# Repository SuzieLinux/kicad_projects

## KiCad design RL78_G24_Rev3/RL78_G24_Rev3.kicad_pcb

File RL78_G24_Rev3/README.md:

This board can use a RL78 G14 or G24, G24 is a newer device which is pin
compatible but uses a different program for configuration

The G14 uses applilet3 and the G24 uses the smart configurator.

I have not tested this board yet but it should work as it is based on other
working boards. If I find issues when I receive the boards I will make an
update to the design

The board runs at 3.3V.
The LCD is Chanruida 1.8 inch TFT LCD 128 × 160 color screen 
ST7735 SPI display LCD module with SD card slot arduino display display lcd

The ethernet adapter is a small board called W5500 SPI to LAN ethernet
network module

The keypad is a 4x5 keypad

The debugger used is E2 Lite. I have an adapter so you can connect the
debugger to it.

Feel free to use this board but if you are going to make money with it be
nice enough to make a donation on my website.

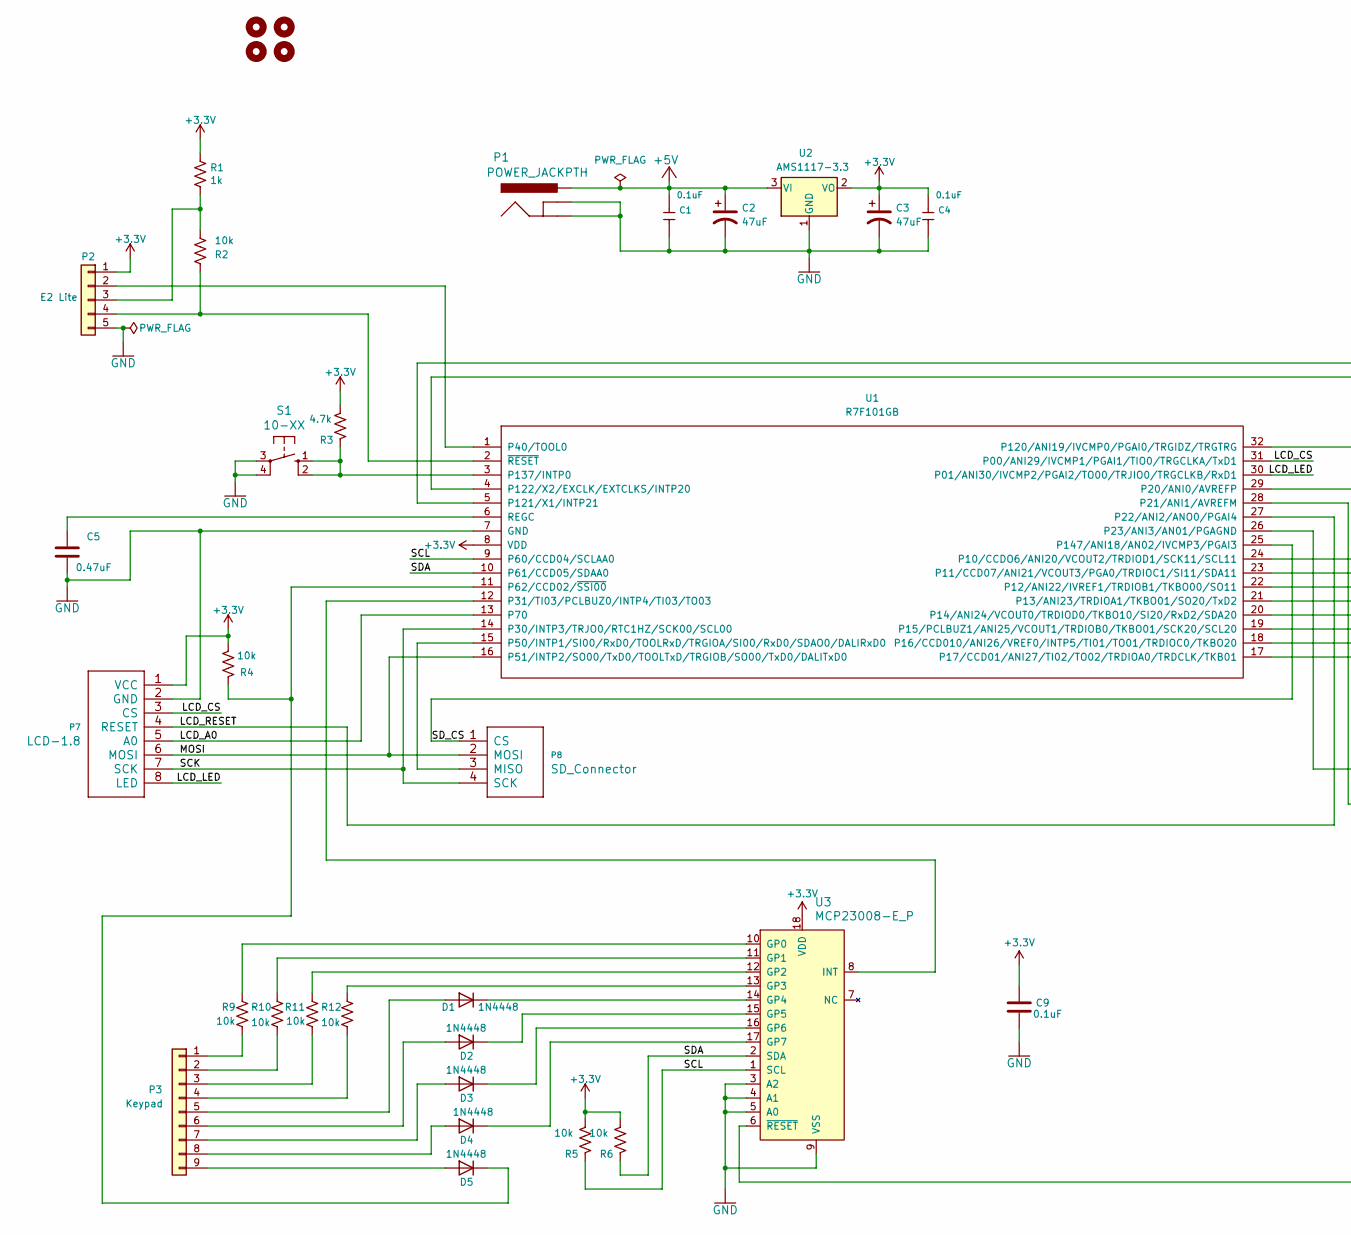
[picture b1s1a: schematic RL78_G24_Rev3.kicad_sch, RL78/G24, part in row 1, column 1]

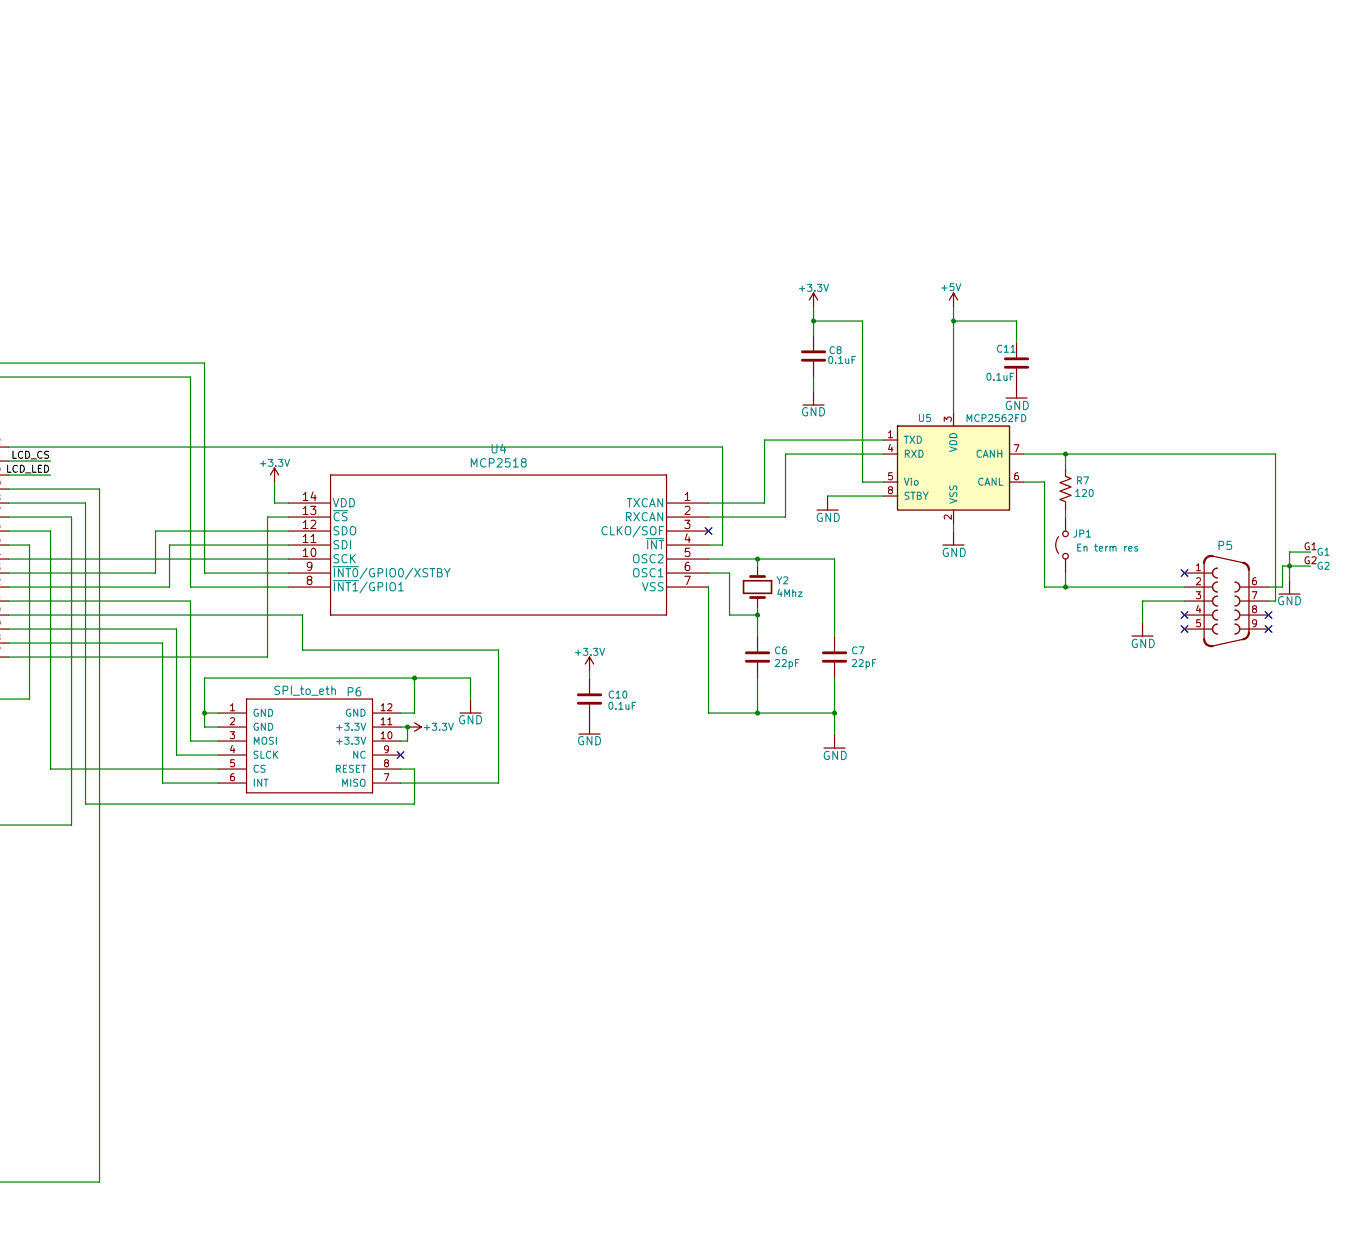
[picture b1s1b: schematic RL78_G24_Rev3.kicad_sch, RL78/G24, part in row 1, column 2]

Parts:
C1, C4: 0.1uF; C_0805_2012Metric_Pad1.18x1.45mm_HandSolder; MPN CC0603KRX7R9BB104; LCSC C14663
C2, C3: 47uF; CP_Radial_D6.3mm_P2.50mm
C5: 0.47uF; C_0805_2012Metric_Pad1.18x1.45mm_HandSolder
C6, C7: 22pF; C_0805_2012Metric_Pad1.18x1.45mm_HandSolder
C8, C9, C10, C11: 0.1uF; C_0805_2012Metric_Pad1.18x1.45mm_HandSolder
D1, D2, D3, D4, D5: 1N4448; D_DO-35_SOD27_P7.62mm_Horizontal
H1, H2, H3, H4: MountingHole; MountingHole_2.7mm_M2.5_DIN965_Pad
JP1: En term res; PinHeader_1x02_P2.54mm_Vertical
P1: POWER_JACKPTH; POWER_JACK_PTH
P2: E2 Lite; PinHeader_1x05_P2.54mm_Vertical
P3: Keypad; PinHeader_1x09_P2.54mm_Vertical
P5: F09HP
P6: SPI_to_eth
P7: LCD-1.8; PinHeader_1x08_P2.54mm_Vertical
P8: SD_Connector; PinHeader_1x04_P2.54mm_Vertical
R1: 1k; R_0805_2012Metric
R2, R9, R10, R11, R12: 10k; R_0805_2012Metric
R3: 4.7k; R_0805_2012Metric_Pad1.20x1.40mm_HandSolder
R4, R5, R6: 10k; R_0805_2012Metric_Pad1.20x1.40mm_HandSolder
R7: 120; R_2512_6332Metric_Pad1.40x3.35mm_HandSolder
S1: 10-XX; B3F-10XX
U1: R7F101GB; LQFP-32_7x7mm
U2: AMS1117-3.3; SOT-223-3_TabPin2; LCSC C6186
U3: MCP23008-E_P; DIP-18_W7.62mm; MPN MCP23008-E/P; Digi-Key_PN MCP23008-E/P-ND
U4: MCP2518; MCP2518FD
U5: MCP2562FD; DIP-8_W7.62mm
Y2: 4Mhz; Crystal_HC49-4H_Vertical

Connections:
+3.3V: C3.1, C4.1, C8.1, C9.1, C10.1, P2.1, P6.10 (+3.3V), P6.11 (+3.3V), P7.1 (VCC), R1.1, R3.2, R4.2, R5.2, R6.2, U1.8 (VDD), U2.2 (VO), U3.18 (VDD), U4.14 (VDD), U5.5 (Vio)
+5V: C1.1, C2.1, C11.1, P1.PWR, U2.3 (VI), U5.3 (VDD)
/LCD_A0: P7.5 (A0), U1.13 (P70)
/LCD_CS: P7.3 (CS), U1.31 (P00/ANI29/IVCMP1/PGAI1/TIO0/TRGCLKA/TxD1)
/LCD_LED: P7.8 (LED), U1.30 (P01/ANI30/IVCMP2/PGAI2/TO00/TRJIO0/TRGC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)
/LCD_RESET: P7.4 (RESET), U1.27 (P22/ANI2/ANO0/PGAI4)
/MOSI: P7.6 (MOSI), P8.2 (MOSI), U1.16 (P51/INTP2/SO00/TxD0/TOOLTxD/TRGIOB/SO00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)
/SCK: P7.7 (SCK), P8.4 (SCK), U1.14 (P30/INTP3/TRJO0/RTC1HZ/SCK00/SCL00)
/SCL: R5.1, U1.9 (P60/CCD04/SCLAA0), U3.1 (SCL)
/SDA: R6.1, U1.10 (P61/CCD05/SDAA0), U3.2 (SDA)
/SD_CS: P8.1 (CS), U1.25 (P147/ANI18/AN02/IVCMP3/PGAI3)
GND: C1.2, C2.2, C3.2, C4.2, C5.2, C6.2, C7.2, C8.2, C9.2, C10.2, C11.2, P1.GND, P1.GNDBREAK, P2.5, P5.3, P5.6, P5.G1, P5.G2, P6.1 (GND), P6.2 (GND), P6.12 (GND), P7.2 (GND), S1.3, S1.4 (P1), U1.7 (GND), U2.1 (GND), U3.3 (A2), U3.4 (A1), U3.5 (A0), U3.9 (VSS), U4.7 (VSS), U5.2 (VSS), U5.8 (STBY)
unnamed: D1.2 (A), P3.5
unnamed: D1.1 (K), U3.14 (GP4)
unnamed: D2.2 (A), P3.6
unnamed: D2.1 (K), U3.15 (GP5)
unnamed: D3.2 (A), P3.7
unnamed: D3.1 (K), U3.16 (GP6)
unnamed: D4.2 (A), P3.8
unnamed: D4.1 (K), U3.17 (GP7)
unnamed: D5.2 (A), P3.9
unnamed: D5.1 (K), R4.1, U1.11 (P62/CCD02/~SSI00)
unnamed: JP1.1 (A), P5.2, U5.6 (CANL)
unnamed: JP1.2 (B), R7.2
unnamed: P2.2, U1.1 (P40/TOOL0)
unnamed: P2.3, R1.2, R2.1
unnamed: P2.4, R2.2, U1.2 (~RESET)
unnamed: P3.1, R9.2
unnamed: P3.2, R10.2
unnamed: P3.3, R11.2
unnamed: P3.4, R12.2
unnamed: P6.5 (CS), U1.26 (P23/ANI3/AN01/PGAGND)
unnamed: P6.6 (INT), U1.18 (P16/CCD010/ANI26/VREF0/INTP5/TI01/TO01/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)
unnamed: P6.7 (MISO), U1.20 (P14/ANI24/VCOUT0/TRDIOD0/TKBO10/SI20/Rx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)
unnamed: P6.3 (MOSI), U1.21 (P13/ANI23/TRDIOA1/TKBO01/SO20/TxD2)
unnamed: P6.8 (RESET), U1.28 (P21/ANI1/AVREFM)
unnamed: P6.4 (SLCK), U1.19 (P15/PCLBUZ1/ANI25/VCOUT1/TRDIOB0/TKBO01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)
unnamed: P8.3 (MISO), U1.15 (P50/INTP1/SI00/RxD0/TOOLRxD/TRGIOA/SI00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)
unnamed: R3.1, S1.1 (S), S1.2 (S1), U1.3 (P137/INTP0)
unnamed: U1.24 (P10/CCDO6/ANI20/VCOUT2/TRDIOD1/SCK11/SC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), U4.10 (SCK)
unnamed: U1.23 (P11/CCD07/ANI21/VCOUT3/PGA0/TRDIOC1/SI1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), U4.12 (SDO)
unnamed: U1.22 (P12/ANI22/IVREF1/TRDIOB1/TKBO00/SO11), U4.11 (SDI)
unnamed: U1.17 (P17/CCD01/ANI27/TI02/TO02/TRDIOA0/TRDCL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), U4.13 (~CS)
unnamed: U1.29 (P20/ANI0/AVREFP), U3.6 (~RESET)
unnamed: U1.12 (P31/TI03/PCLBUZ0/INTP4/TI03/TO03), U3.8 (INT)
unnamed: U1.32 (P120/ANI19/IVCMP0/PGAI0/TRGIDZ/TRGTRG), U4.4 (~INT)
unnamed: U1.5 (P121/X1/INTP21), U4.9 (~INT0/GPIO0/XSTBY)
unnamed: U1.4 (P122/X2/EXCLK/EXTCLKS/INTP20), U4.8 (~INT1/GPIO1)
unnamed: C5.1, U1.6 (REGC)
unnamed: R9.1, U3.10 (GP0)
unnamed: R10.1, U3.11 (GP1)
unnamed: R11.1, U3.12 (GP2)
unnamed: R12.1, U3.13 (GP3)
unnamed: C6.1, U4.6 (OSC1), Y2.2
unnamed: C7.1, U4.5 (OSC2), Y2.1
unnamed: U4.2 (RXCAN), U5.4 (RXD)
unnamed: U4.1 (TXCAN), U5.1 (TXD)
unnamed: P5.7, R7.1, U5.7 (CANH)

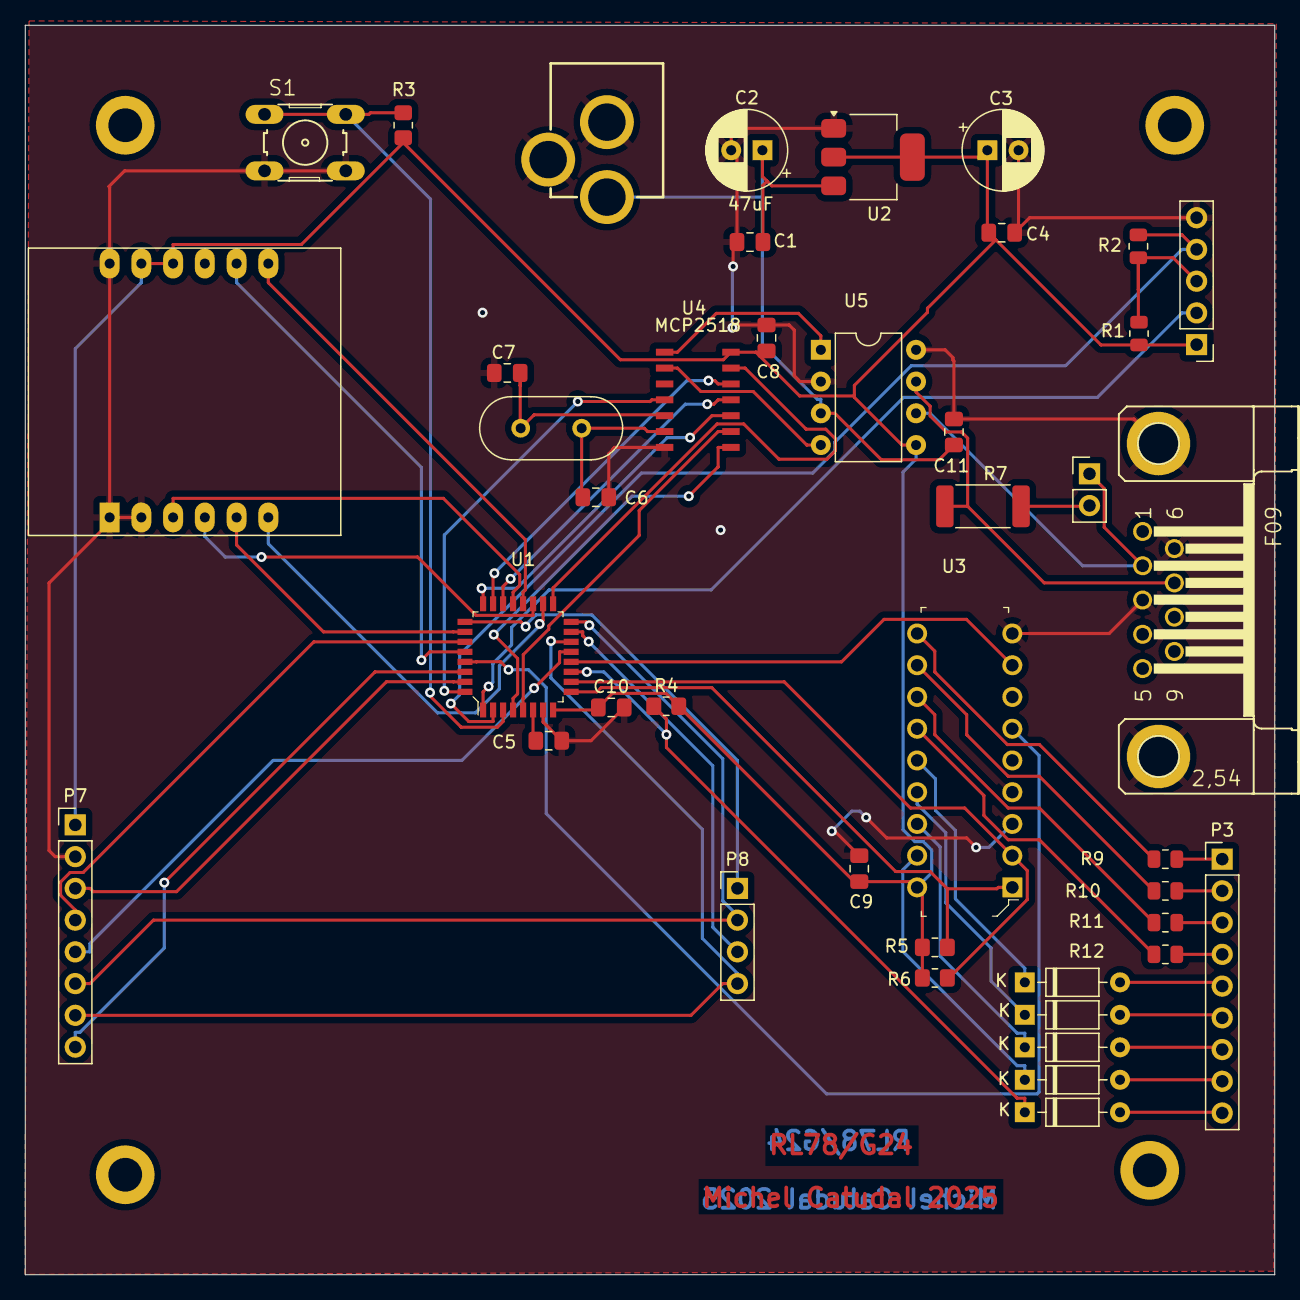
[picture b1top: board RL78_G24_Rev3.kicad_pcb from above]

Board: 2 copper layers, 100.0 x 100.0 mm, 46 parts (0 on the bottom side), 58 nets.

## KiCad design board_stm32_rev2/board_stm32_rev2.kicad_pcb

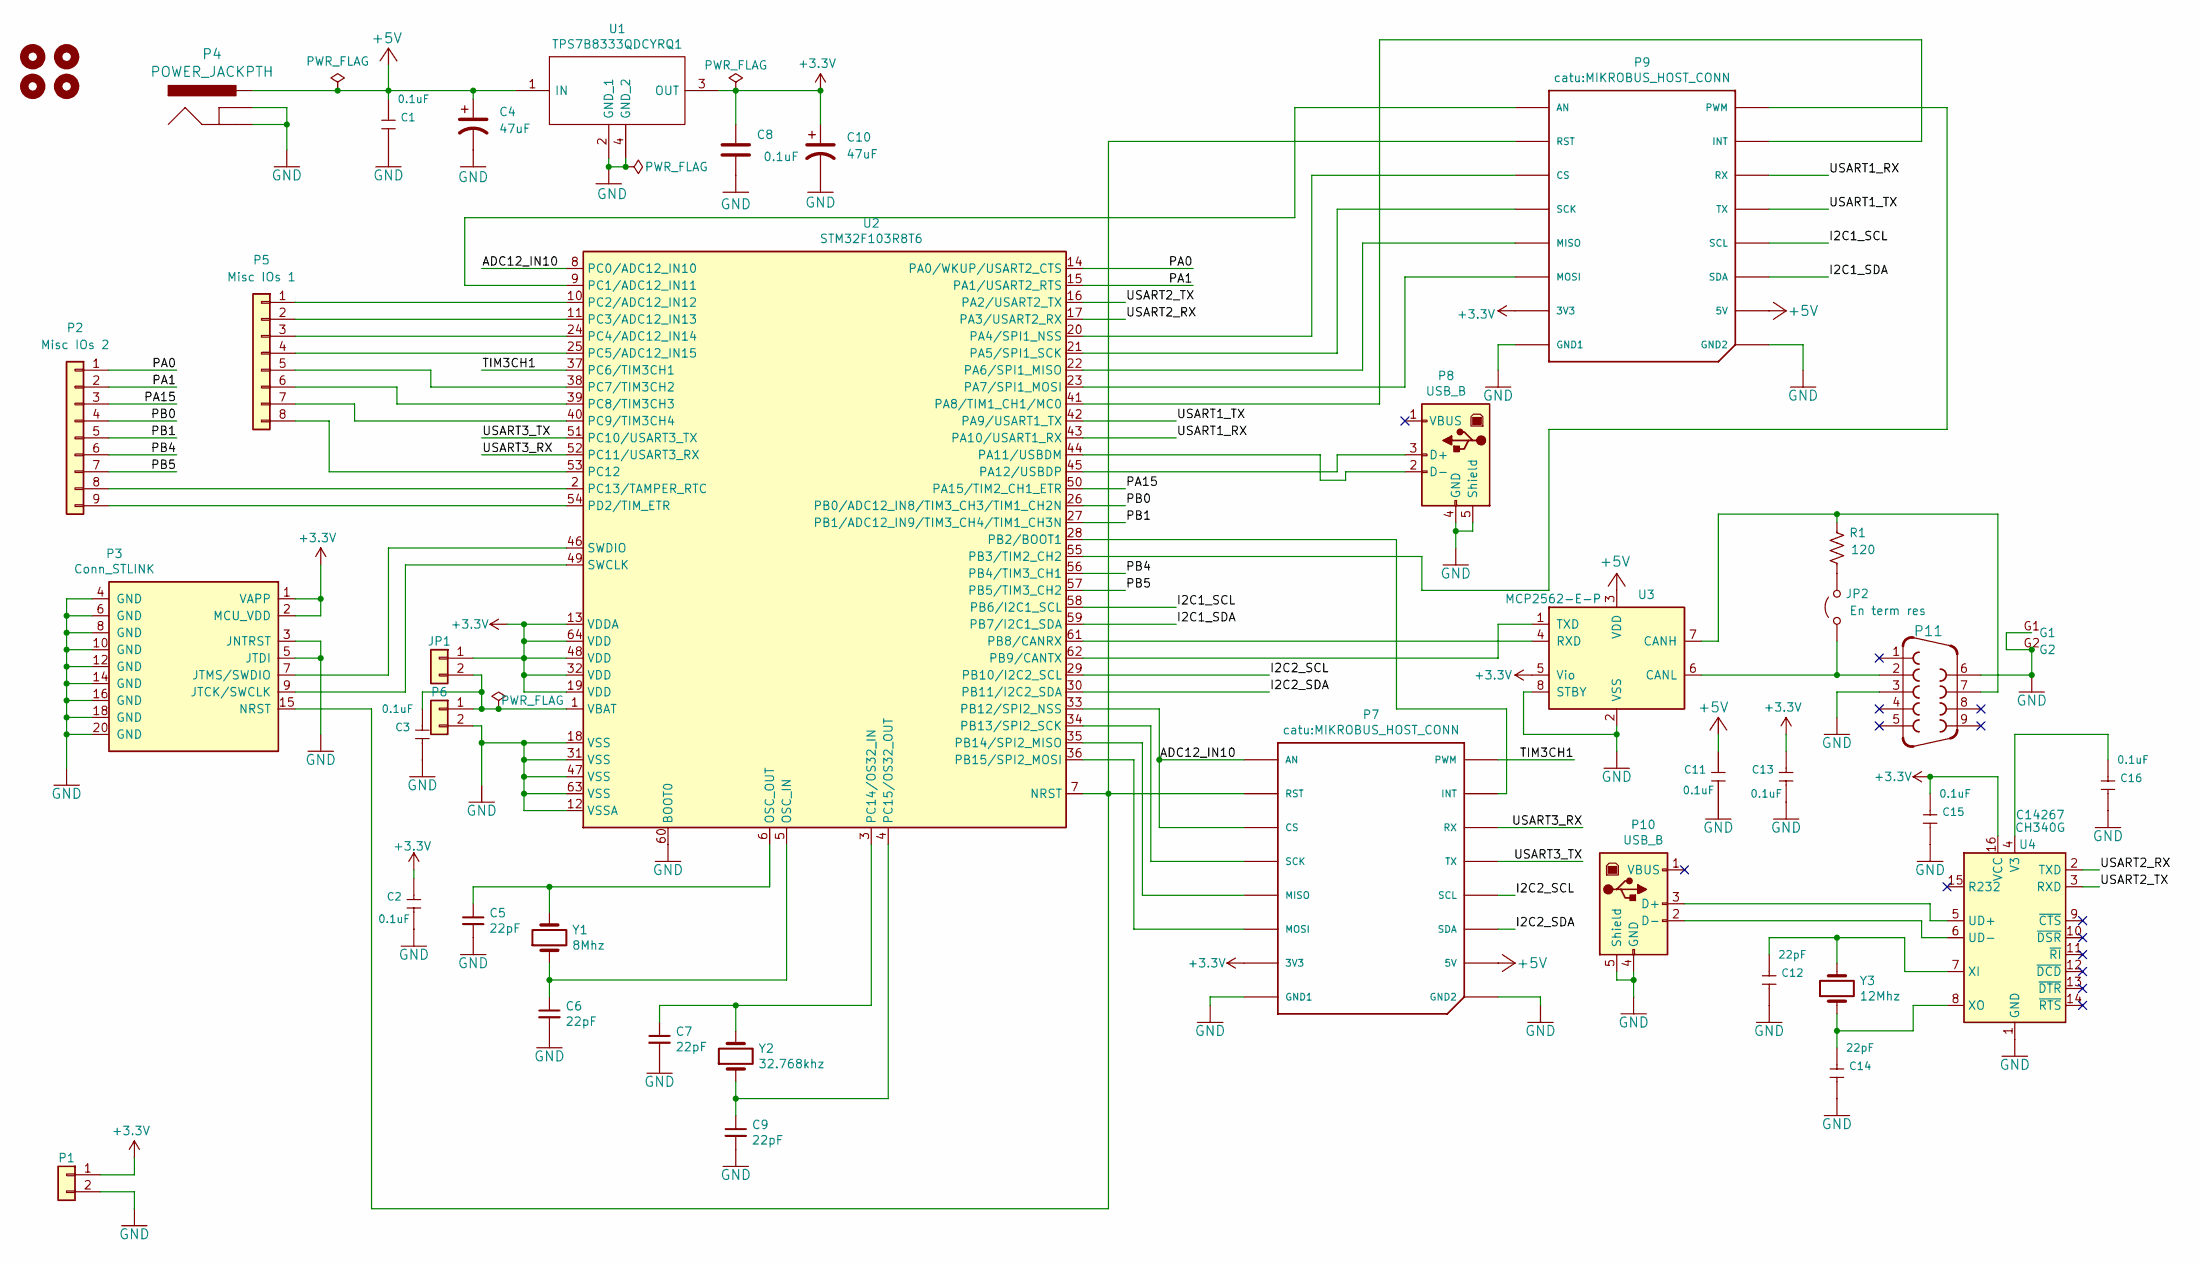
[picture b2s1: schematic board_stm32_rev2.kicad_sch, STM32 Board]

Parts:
C1, C2, C3, C11, C13, C15, C16: 0.1uF; C_0805_2012Metric_Pad1.18x1.45mm_HandSolder; MPN CC0603KRX7R9BB104; LCSC C14663
C4, C10: 47uF; CP_Radial_D6.3mm_P2.50mm
C5, C6, C7, C9: 22pF; C_0805_2012Metric_Pad1.18x1.45mm_HandSolder; LCSC C1648
C8: 0.1uF; C_0805_2012Metric_Pad1.18x1.45mm_HandSolder
C12, C14: 22pF; C_0805_2012Metric_Pad1.18x1.45mm_HandSolder; MPN CC0603KRX7R9BB104; LCSC C1562
H1, H2, H3, H4: MountingHole; MountingHole_2.7mm_M2.5_DIN965_Pad
JP1: +3.3 V on battery; PinHeader_1x02_P2.54mm_Vertical
JP2: En term res; PinHeader_1x02_P2.54mm_Vertical
P1: +3.3V Supply; PinHeader_1x02_P2.54mm_Vertical
P2: Misc IOs 2; PinHeader_1x09_P2.54mm_Vertical
P3: Conn_STLINK; IDC-Header_2x10_P2.54mm_Vertical
P4: POWER_JACKPTH; POWER_JACK_PTH
P5: Misc IOs 1; PinHeader_1x08_P2.54mm_Vertical
P6: Battery; PinSocket_1x02_P1.27mm_Vertical_SMD_Pin1Left
P7, P9: catu:MIKROBUS_HOST_CONN; MIKROBUS_HOST_CONN
P8, P10: USB_B; USB_B_OST_USB-B1HSxx_Horizontal
P11: F09HP
R1: 120; R_2512_6332Metric_Pad1.40x3.35mm_HandSolder
U1: TPS7B8333QDCYRQ1; SOT230P700X180-4N
U2: STM32F103R8T6; LQFP-64_10x10mm_P0.5mm; LCSC C46034
U3: MCP2562-E-P; DIP-8_W7.62mm
U4: CH340G; SOIC-16_3.9x9.9mm_P1.27mm; LCSC C14267
Y1: 8Mhz; Crystal_HC49-4H_Vertical
Y2: 32.768khz; Crystal_DS15_D1.5mm_L5.0mm_Horizontal
Y3: 12Mhz; Crystal_HC49-4H_Vertical

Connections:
+3.3V: C2.1, C8.1, C10.1, C13.1, C15.1, JP1.1, P1.1, P3.1 (VAPP), P3.2 (MCU_VDD), P7.P7 (3V3), P9.P7 (3V3), U1.3 (OUT), U2.13 (VDDA), U2.19 (VDD), U2.32 (VDD), U2.48 (VDD), U2.64 (VDD), U3.5 (Vio), U4.16 (VCC)
+5V: C1.1, C4.1, C11.1, P4.PWR, P7.P10 (5V), P9.P10 (5V), U1.1 (IN), U3.3 (VDD)
/ADC12_IN10: P7.P1 (AN), P7.P3 (CS), U2.8 (PC0/ADC12_IN10), U2.33 (PB12/SPI2_NSS)
/I2C1_SCL: P9.P12 (SCL), U2.58 (PB6/I2C1_SCL)
/I2C1_SDA: P9.P11 (SDA), U2.59 (PB7/I2C1_SDA)
/I2C2_SCL: P7.P12 (SCL), U2.29 (PB10/I2C2_SCL)
/I2C2_SDA: P7.P11 (SDA), U2.30 (PB11/I2C2_SDA)
/PA0: P2.1, U2.14 (PA0/WKUP/USART2_CTS)
/PA1: P2.2, U2.15 (PA1/USART2_RTS)
/PA15: P2.3, U2.50 (PA15/TIM2_CH1_ETR)
/PB0: P2.4, U2.26 (PB0/ADC12_IN8/TIM3_CH3/TIM1_CH2N)
/PB1: P2.5, U2.27 (PB1/ADC12_IN9/TIM3_CH4/TIM1_CH3N)
/PB4: P2.6, U2.56 (PB4/TIM3_CH1)
/PB5: P2.7, U2.57 (PB5/TIM3_CH2)
/TIM3CH1: P7.P16 (PWM), U2.37 (PC6/TIM3CH1)
/USART1_RX: P9.P14 (RX), U2.43 (PA10/USART1_RX)
/USART1_TX: P9.P13 (TX), U2.42 (PA9/USART1_TX)
/USART2_RX: U2.17 (PA3/USART2_RX), U4.2 (TXD)
/USART2_TX: U2.16 (PA2/USART2_TX), U4.3 (RXD)
/USART3_RX: P7.P14 (RX), U2.52 (PC11/USART3_RX)
/USART3_TX: P7.P13 (TX), U2.51 (PC10/USART3_TX)
GND: C1.2, C2.2, C3.2, C4.2, C5.2, C6.2, C7.2, C8.2, C9.2, C10.2, C11.2, C12.2, C13.2, C14.2, C15.2, C16.2, P1.2, P3.3 (JNTRST), P3.4 (GND), P3.5 (JTDI), P3.6 (GND), P3.8 (GND), P3.10 (GND), P3.12 (GND), P3.14 (GND), P3.16 (GND), P3.18 (GND), P3.20 (GND), P4.GND, P4.GNDBREAK, P6.2, P7.P8 (GND1), P7.P9 (GND2), P8.4 (GND), P8.5 (Shield), P9.P8 (GND1), P9.P9 (GND2), P10.4 (GND), P10.5 (Shield), P11.3, P11.6, P11.G1, P11.G2, U1.2 (GND_1), U1.4 (GND_2), U2.12 (VSSA), U2.18 (VSS), U2.31 (VSS), U2.47 (VSS), U2.60 (BOOT0), U2.63 (VSS), U3.2 (VSS), U3.8 (STBY), U4.1 (GND)
unnamed: C3.1, JP1.2, P6.1, U2.1 (VBAT)
unnamed: JP2.1 (A), P11.2, U3.6 (CANL)
unnamed: JP2.2 (B), R1.2
unnamed: P2.8, U2.2 (PC13/TAMPER_RTC)
unnamed: P2.9, U2.54 (PD2/TIM_ETR)
unnamed: P3.9 (JTCK/SWCLK), U2.49 (SWCLK)
unnamed: P3.7 (JTMS/SWDIO), U2.46 (SWDIO)
unnamed: P3.15 (NRST), P7.P2 (RST), P9.P2 (RST), U2.7 (NRST)
unnamed: P5.1, U2.10 (PC2/ADC12_IN12)
unnamed: P5.2, U2.11 (PC3/ADC12_IN13)
unnamed: P5.3, U2.24 (PC4/ADC12_IN14)
unnamed: P5.4, U2.25 (PC5/ADC12_IN15)
unnamed: P5.5, U2.38 (PC7/TIM3CH2)
unnamed: P5.6, U2.39 (PC8/TIM3CH3)
unnamed: P5.7, U2.40 (PC9/TIM3CH4)
unnamed: P5.8, U2.53 (PC12)
unnamed: P7.P15 (INT), U2.28 (PB2/BOOT1)
unnamed: P7.P5 (MISO), U2.35 (PB14/SPI2_MISO)
unnamed: P7.P6 (MOSI), U2.36 (PB15/SPI2_MOSI)
unnamed: P7.P4 (SCK), U2.34 (PB13/SPI2_SCK)
unnamed: P8.3 (D+), U2.45 (PA12/USBDP)
unnamed: P8.2 (D-), U2.44 (PA11/USBDM)
unnamed: P9.P1 (AN), U2.9 (PC1/ADC12_IN11)
unnamed: P9.P3 (CS), U2.20 (PA4/SPI1_NSS)
unnamed: P9.P15 (INT), U2.41 (PA8/TIM1_CH1/MC0)
unnamed: P9.P5 (MISO), U2.22 (PA6/SPI1_MISO)
unnamed: P9.P6 (MOSI), U2.23 (PA7/SPI1_MOSI)
unnamed: P9.P16 (PWM), U2.55 (PB3/TIM2_CH2)
unnamed: P9.P4 (SCK), U2.21 (PA5/SPI1_SCK)
unnamed: P10.3 (D+), U4.5 (UD+)
unnamed: P10.2 (D-), U4.6 (UD-)
unnamed: C6.1, U2.5 (OSC_IN), Y1.1
unnamed: C5.1, U2.6 (OSC_OUT), Y1.2
unnamed: U2.61 (PB8/CANRX), U3.4 (RXD)
unnamed: U2.62 (PB9/CANTX), U3.1 (TXD)
unnamed: C7.1, U2.3 (PC14/OS32_IN), Y2.2
unnamed: C9.1, U2.4 (PC15/OS32_OUT), Y2.1
unnamed: P11.7, R1.1, U3.7 (CANH)
unnamed: C16.1, U4.4 (V3)
unnamed: C12.1, U4.7 (XI), Y3.2
unnamed: C14.1, U4.8 (XO), Y3.1

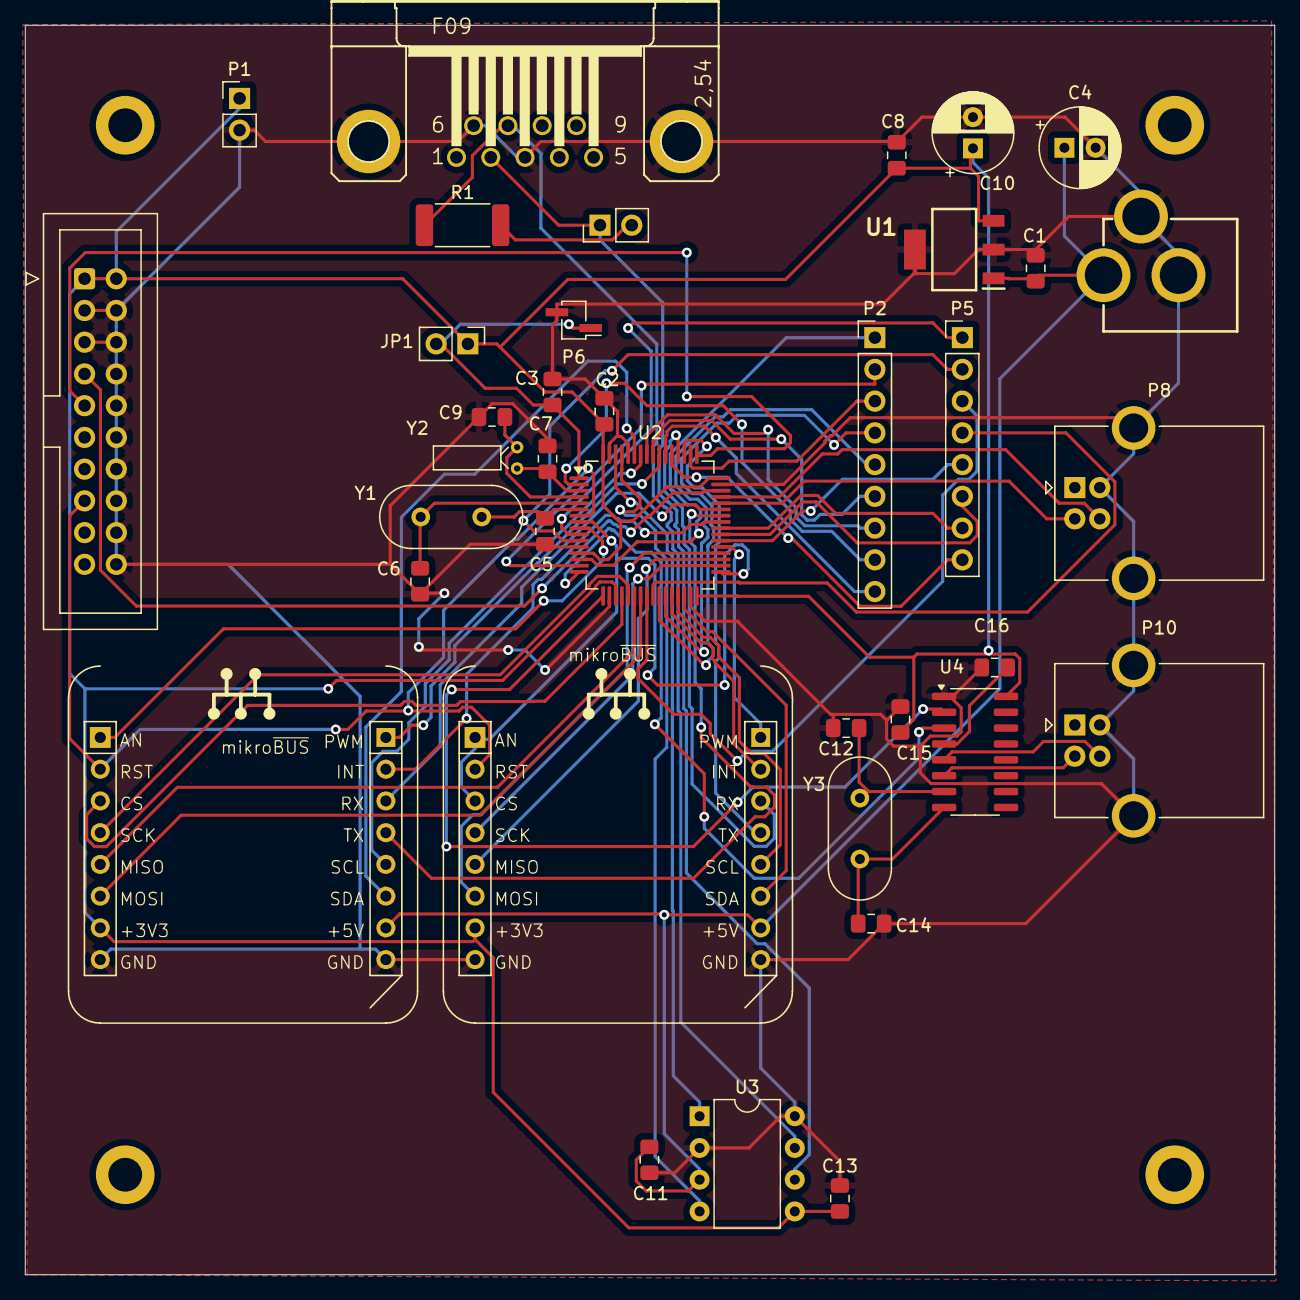
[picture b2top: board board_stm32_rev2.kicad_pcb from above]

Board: 2 copper layers, 100.0 x 100.0 mm, 41 parts (0 on the bottom side), 63 nets.

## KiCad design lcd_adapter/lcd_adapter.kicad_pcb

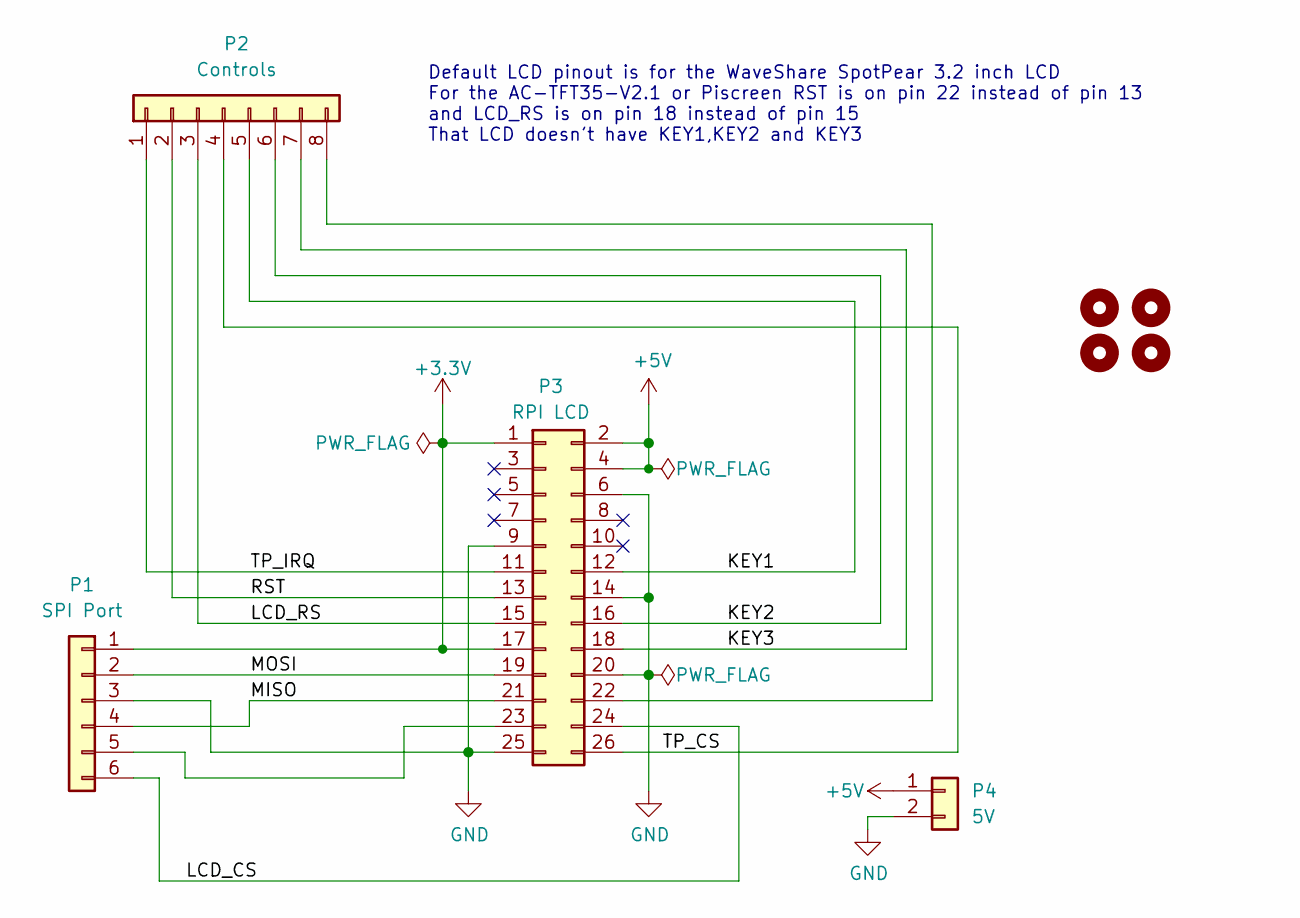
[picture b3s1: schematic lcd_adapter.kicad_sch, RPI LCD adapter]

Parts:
H1, H2, H3, H4: MountingHole; MountingHole_2.7mm_M2.5_DIN965_Pad
P1: SPI Port; PinHeader_1x06_P2.54mm_Vertical
P2: Controls; PinHeader_1x08_P2.54mm_Vertical
P3: RPI LCD; PinSocket_2x13_P2.54mm_Vertical
P4: 5V; PinHeader_1x02_P2.54mm_Vertical

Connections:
+3.3V: P1.1, P3.1, P3.17
+5V: P3.2, P3.4, P4.1
/KEY1: P2.5, P3.12
/KEY2: P2.6, P3.16
/KEY3: P2.7, P3.18
/LCD_CS: P1.6, P3.24
/LCD_RS: P2.3, P3.15
/MISO: P1.4, P3.21
/MOSI: P1.2, P3.19
/RST: P2.2, P3.13
/TP_CS: P2.4, P3.26
/TP_IRQ: P2.1, P3.11
GND: P1.3, P3.6, P3.9, P3.14, P3.20, P3.25, P4.2
unnamed: P1.5, P3.23
unnamed: P2.8, P3.22

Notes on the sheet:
Default LCD pinout is for the WaveShare SpotPear 3.2 inch LCD For the AC-TFT35-V2.1 or Piscreen RST is on pin 22 instead of pin 13 and LCD_RS is on pin 18 instead of pin 15 That LCD doesn't have KEY1,KEY2 and KEY3

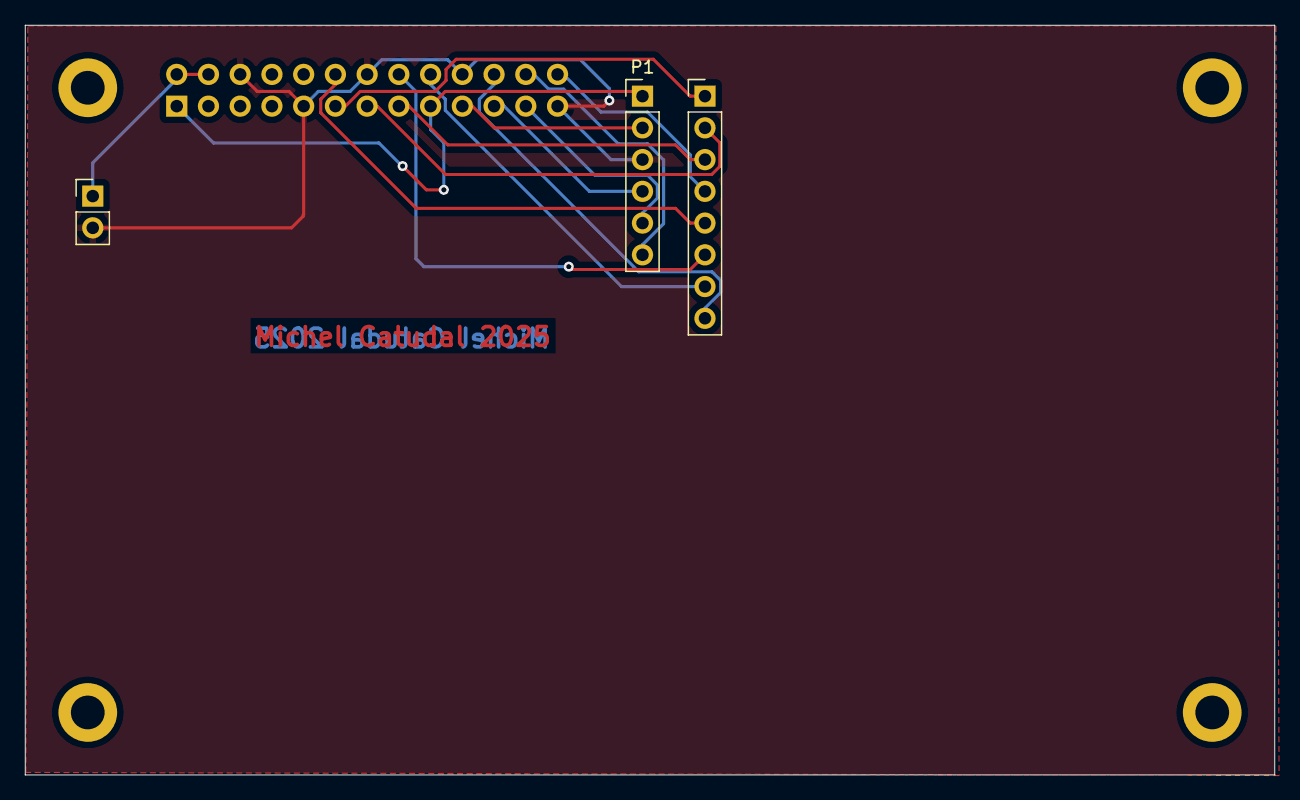
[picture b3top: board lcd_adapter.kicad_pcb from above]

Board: 2 copper layers, 100.0 x 60.0 mm, 8 parts (1 on the bottom side), 15 nets.

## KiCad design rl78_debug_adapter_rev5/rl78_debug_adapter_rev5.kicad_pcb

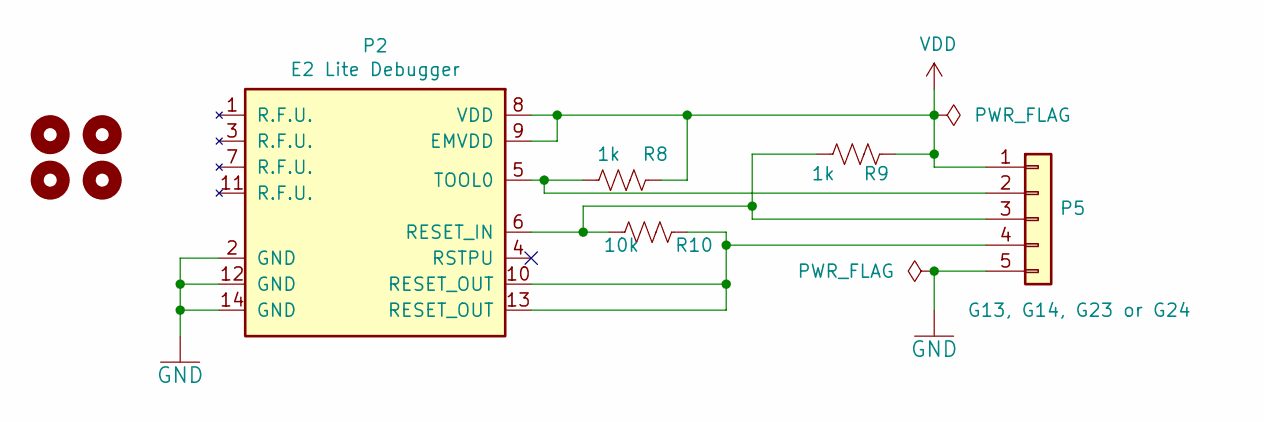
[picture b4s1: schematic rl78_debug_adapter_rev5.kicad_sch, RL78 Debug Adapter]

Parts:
H1, H2, H3, H4: MountingHole; MountingHole_2.7mm_M2.5_DIN965_Pad
P2: E2 Lite Debugger; IDC-Header_2x07_P2.54mm_Vertical
P5: G13, G14, G23 or G24; PinHeader_1x05_P2.54mm_Vertical
R8, R9: 1k; R_Axial_DIN0414_L11.9mm_D4.5mm_P15.24mm_Horizontal
R10: 10k; R_Axial_DIN0414_L11.9mm_D4.5mm_P15.24mm_Horizontal

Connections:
GND: P2.2 (GND), P2.12 (GND), P2.14 (GND), P5.5
unnamed: P2.6 (RESET_IN), P5.3, R9.2, R10.2
unnamed: P2.5 (TOOL0), P5.2, R8.2
unnamed: P2.10 (RESET_OUT), P2.13 (RESET_OUT), P5.4, R10.1
VDD: P2.8 (VDD), P2.9 (EMVDD), P5.1, R8.1, R9.1

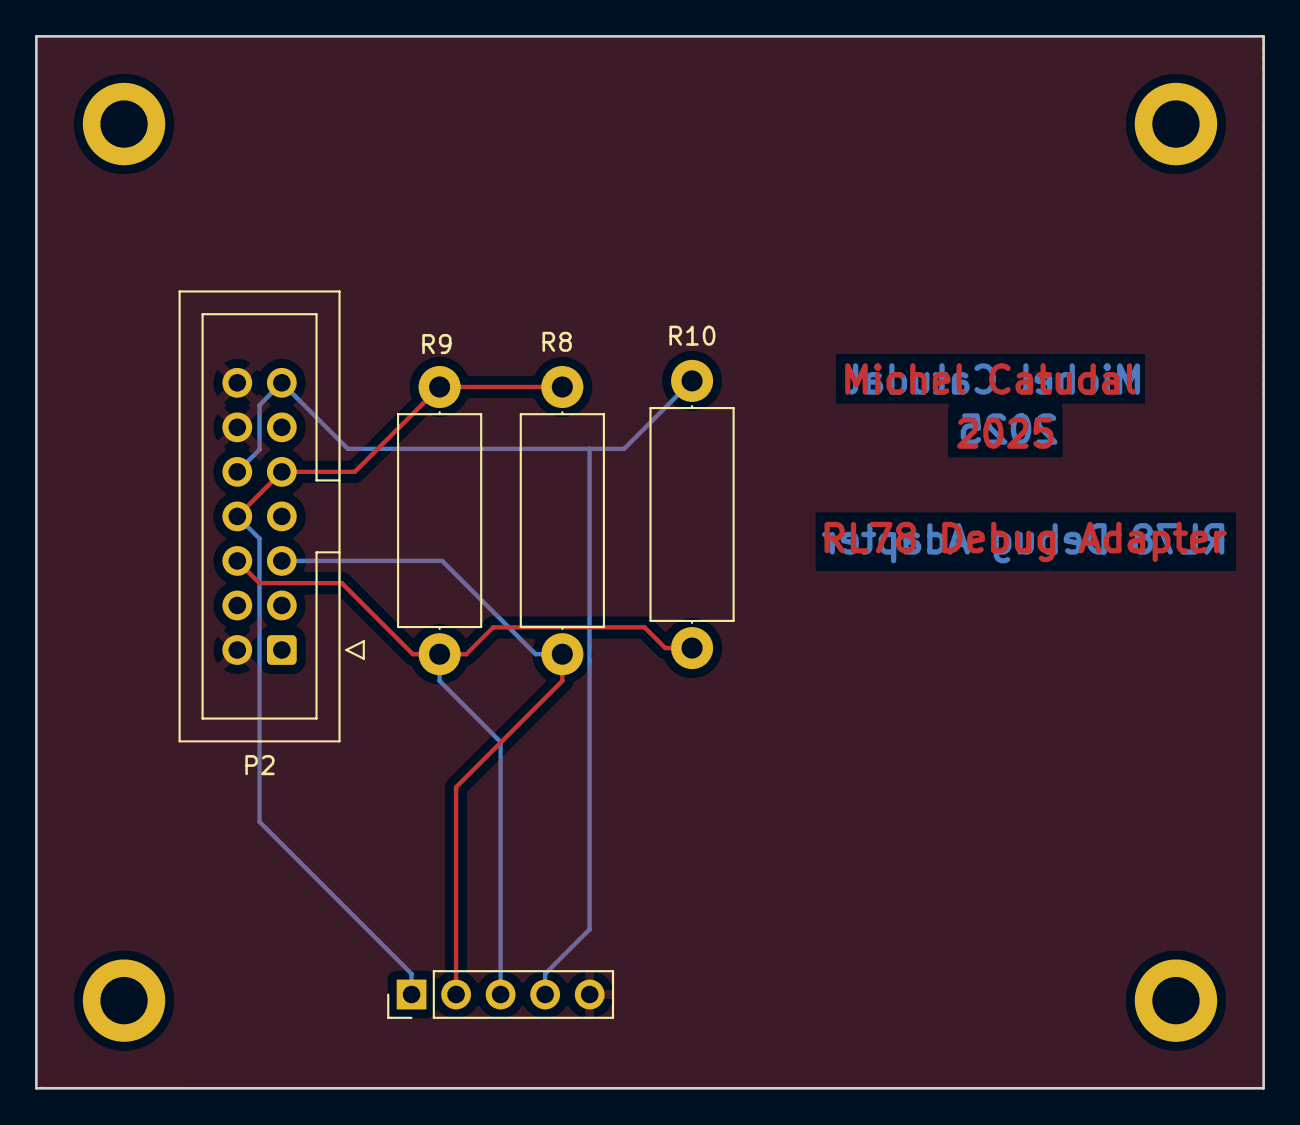
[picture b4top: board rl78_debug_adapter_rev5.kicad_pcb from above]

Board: 2 copper layers, 70.0 x 60.0 mm, 9 parts (0 on the bottom side), 5 nets.

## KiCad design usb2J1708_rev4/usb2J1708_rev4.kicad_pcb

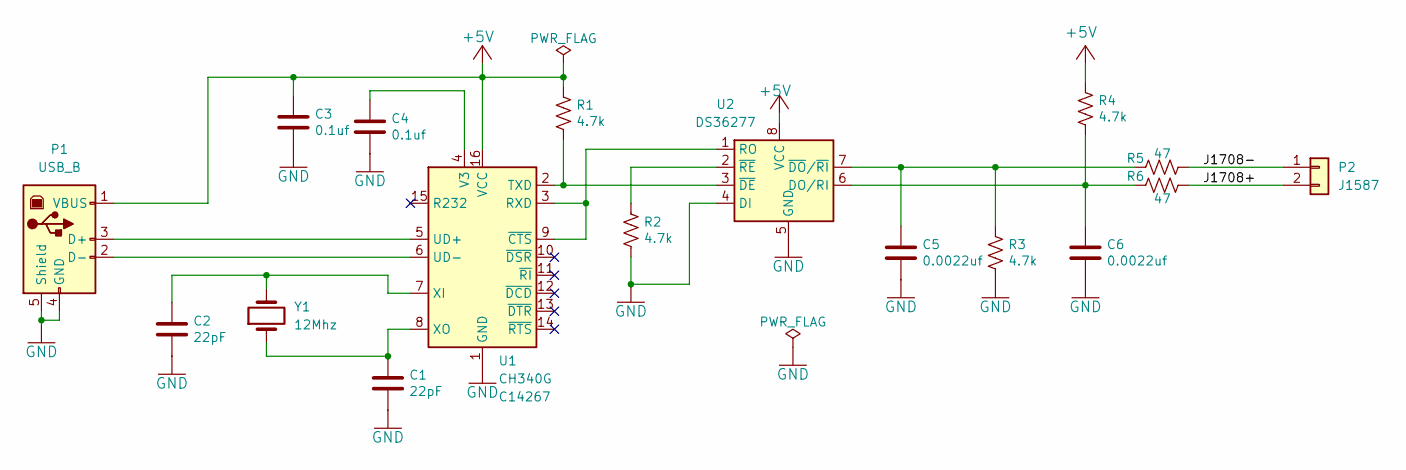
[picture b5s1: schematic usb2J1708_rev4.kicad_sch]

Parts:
C1, C2: 22pF; C_0805_2012Metric_Pad1.18x1.45mm_HandSolder
C3, C4: 0.1uf; C_0805_2012Metric_Pad1.18x1.45mm_HandSolder
C5, C6: 0.0022uf; C_0805_2012Metric_Pad1.18x1.45mm_HandSolder
P1: USB_B; USB_B_Lumberg_2411_02_Horizontal
P2: J1587; PinHeader_1x02_P2.54mm_Vertical
R1, R2: 4.7k; R_0805_2012Metric_Pad1.20x1.40mm_HandSolder
R3, R4: 4.7k; R_1206_3216Metric_Pad1.30x1.75mm_HandSolder
R5, R6: 47; R_2512_6332Metric_Pad1.40x3.35mm_HandSolder
U1: CH340G; SOIC-16_3.9x9.9mm_P1.27mm; LCSC C14267
U2: DS36277; SOIC-8_3.9x4.9mm_P1.27mm
Y1: 12Mhz; Crystal_HC49-4H_Vertical

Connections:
+5V: C3.1, P1.1 (VBUS), R1.1, R4.1, U1.16 (VCC), U2.8 (VCC)
/J1708+: P2.2, R6.1
/J1708-: P2.1, R5.1
GND: C1.2, C2.2, C3.2, C4.2, C5.2, C6.2, P1.4 (GND), P1.5 (Shield), R2.2, R3.2, U1.1 (GND), U2.4 (DI), U2.5 (GND)
unnamed: P1.3 (D+), U1.5 (UD+)
unnamed: P1.2 (D-), U1.6 (UD-)
unnamed: U1.3 (RXD), U1.9 (~CTS), U2.1 (RO)
unnamed: R1.2, U1.2 (TXD), U2.3 (~DE)
unnamed: C4.1, U1.4 (V3)
unnamed: C2.1, U1.7 (XI), Y1.2
unnamed: C1.1, U1.8 (XO), Y1.1
unnamed: C6.1, R4.2, R6.2, U2.6 (DO/RI)
unnamed: C5.1, R3.1, R5.2, U2.7 (~DO/~RI)
unnamed: R2.1, U2.2 (~RE)
